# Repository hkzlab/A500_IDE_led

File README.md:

# A500 IDE activity led injector

## DISCLAIMER

Any use of this project is **under your own responsibility**.
You will be responsible of checking the correct construction and functionality of your board.
By using this project You will agree that I cannot be held responsible if it will destroy any of your devices, damage your computer, burn down your house or whatever.

## Introduction

This board reproduces the same circuit that the A500 uses to flash the "DRIVE" LED when the `/MTR0` signal is toggled, and puts itself in parallel to that 
by being installed between the keyboard and the connector on the motherboard.

It is useful to have the LED blink for other activity beside the floppy's, ideally, IDE hard drive activity.

The IDE activity signal must then be taken from the IDE connector, on a 44 pin connector, it is on pin 39.

### Ordering the boards

You can order the board for this project at [PCBWay](https://www.pcbway.com/project/shareproject/A500_IDE_LED_mod_board_fed31fc6.html) and support me or download 
the gerbers and have them printed wherever you like!!!

## Hardware

The board was designed with [KiCad](https://kicad.org/) EDA.

### Bill of Materials

| Component              | Qty | Type / Value                     | Notes                                                                |
| ---------------------- | --- | -------------------------------- | -------------------------------------------------------------------- |
| R1                     |  1  | 4.7K 1/4W THT resistor           |                                                                      |
| R2                     |  1  | 10K 1/4W THT resistor            |                                                                      |
| Q1                     |  1  | 2N3906 TO-92 transistor          |                                                                      |
| J1                     |  1  | 8pin, 2.54mm pitch socket        | Mount on the underside of the board                                  |
| J2                     |  1  | 8pin, 2.54mm pitch header        | straight pins are fine, use right angled ones for a better fit       |
| J3                     |  1  | 1pin                             | Optional, you can solder the activity wire here or use a header      |
| U1                     |  1  | 74AHCT1G07 SOT-353               | Optional, see note below                                             |
| R3                     |  1  | 10K 0805 SMD resistor            | Optional, see note below                                             |
| C1                     |  1  | 100nF/16V 0805 SMD capacitor     | Optional, see note below                                             |

Components U1, R3 and C1 implement a buffer for the /IDE_ACTIVITY signal, which is useful if you notice that the activity LED in the A500 remains faintly lit
when the adapter is installed (happens when the high level for the signal is not high enough to completely shut the transistor off).

If these components are omitted, close the jumper JP1.

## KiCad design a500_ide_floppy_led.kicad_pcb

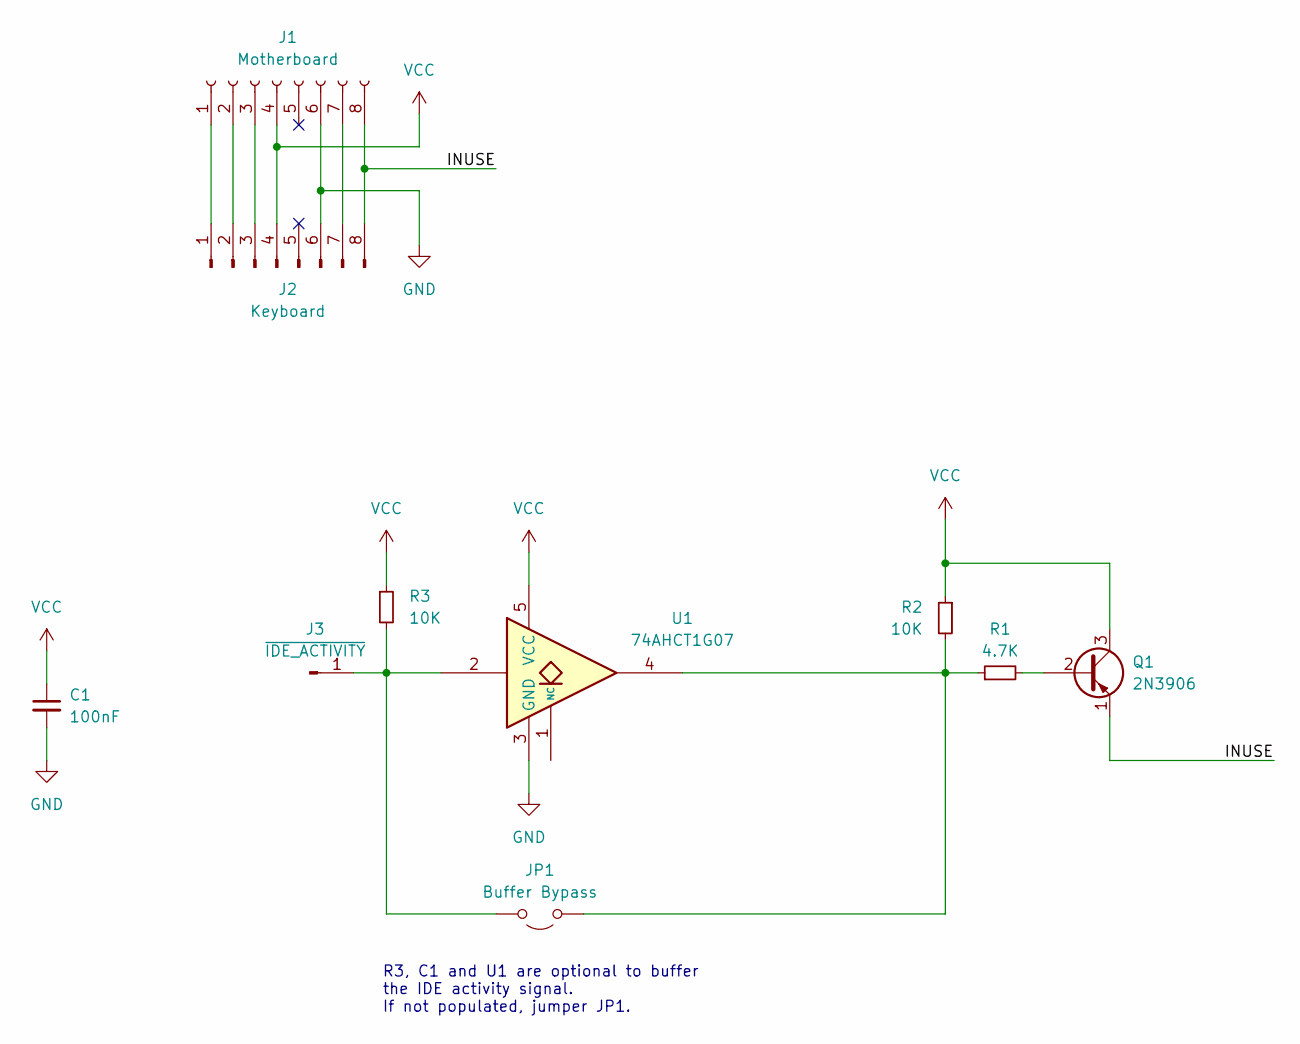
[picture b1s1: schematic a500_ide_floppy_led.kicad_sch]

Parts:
C1: 100nF; C_0805_2012Metric_Pad1.18x1.45mm_HandSolder
J1: Motherboard; PinSocket_1x08_P2.54mm_Vertical
J2: Keyboard; PinHeader_1x08_P2.54mm_Vertical
J3: ~{IDE_ACTIVITY}; PinHeader_1x01_P2.54mm_Vertical
JP1: Buffer Bypass; SolderJumper-2_P1.3mm_Open_RoundedPad1.0x1.5mm
Q1: 2N3906; TO-92_Inline
R1: 4.7K; R_Axial_DIN0207_L6.3mm_D2.5mm_P10.16mm_Horizontal
R2: 10K; R_Axial_DIN0207_L6.3mm_D2.5mm_P10.16mm_Horizontal
R3: 10K; R_0805_2012Metric_Pad1.20x1.40mm_HandSolder
U1: 74AHCT1G07; SOT-353_SC-70-5_Handsoldering

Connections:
/INUSE: J1.8, J2.8, Q1.1 (E)
GND: C1.2, J1.6, J2.6, U1.3 (GND)
unnamed: J1.1, J2.1
unnamed: J1.2, J2.2
unnamed: J1.3, J2.3
unnamed: J1.7, J2.7
unnamed: J3.1, JP1.2 (B), R3.2, U1.2
unnamed: JP1.1 (A), R1.1, R2.2, U1.4
unnamed: Q1.2 (B), R1.2
VCC: C1.1, J1.4, J2.4, Q1.3 (C), R2.1, R3.1, U1.5 (VCC)

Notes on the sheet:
R3, C1 and U1 are optional to buffer the IDE activity signal. If not populated, jumper JP1.

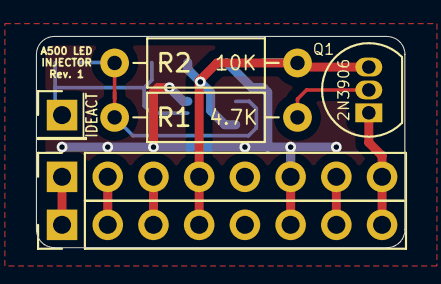
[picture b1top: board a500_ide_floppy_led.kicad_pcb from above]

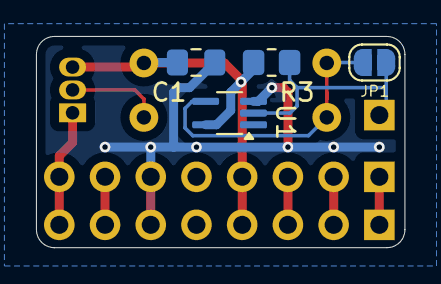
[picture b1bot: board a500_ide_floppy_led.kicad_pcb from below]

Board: 2 copper layers, 20.5 x 11.7 mm, 10 parts (4 on the bottom side), 10 nets.

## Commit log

2024-12-08 Add ide activity floppy led injector
2024-12-08 Tweak the silkscreen
2024-12-08 Slightly shrink the board
2024-12-08 Increase trace width for INUSE
2024-12-08 Increase track width
2025-01-26 Update README, add pics
2025-01-26 Update the README with ordering info
2025-01-26 Fix measure in readme
2025-01-27 Add untested rev.1 that buffers the signal
2025-02-14 Remove rev_0 gerbers
